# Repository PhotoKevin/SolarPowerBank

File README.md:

# SolarPowerBank
Solar charged power bank

This is a replacement for one I had cobbled together using some ready made boards. The redesign is intended to
address two major areas:

* Airline compatible. Commercial units tend to be all-in-one. You can't separate the battery pack from the solar
panel. This is a problem since you can't put LIon batteries in checked luggage. This unit is designed to be
separate from the panel.
* Fast charge. The old one could only do 500mA charging.  The idea is to keep a battery charging all day and
be able to quick charge a phone.
* Designed to go in a box. If you build something from pre-made boards such as those from AdaFruit, the connectors
are all on the board. This is set up to use "panel mount" connectors.

## Hardware design
The design works around two integrated circuits. A Texas Instruments BQ25185 and an iSmartWare SW2303.

### BQ25185
The TI BQ25185 is a multi-chemistry battery charging controller. The key feature for this application is that it's solar compatible. Solar panels will shut down if you try to draw too much current from them. This can lead to an infinite start/stop cycle which is inefficient and will reduce battery life. [Datasheet](http://www.ti.com/lit/ds/symlink/bq51050b.pdf)

### SW2303
The iSmartWare SW2303 is a fast USB charging module. [Datasheet](http://www.ismartware.cn/upload/goods/20220721/202207211507542921.pdf)

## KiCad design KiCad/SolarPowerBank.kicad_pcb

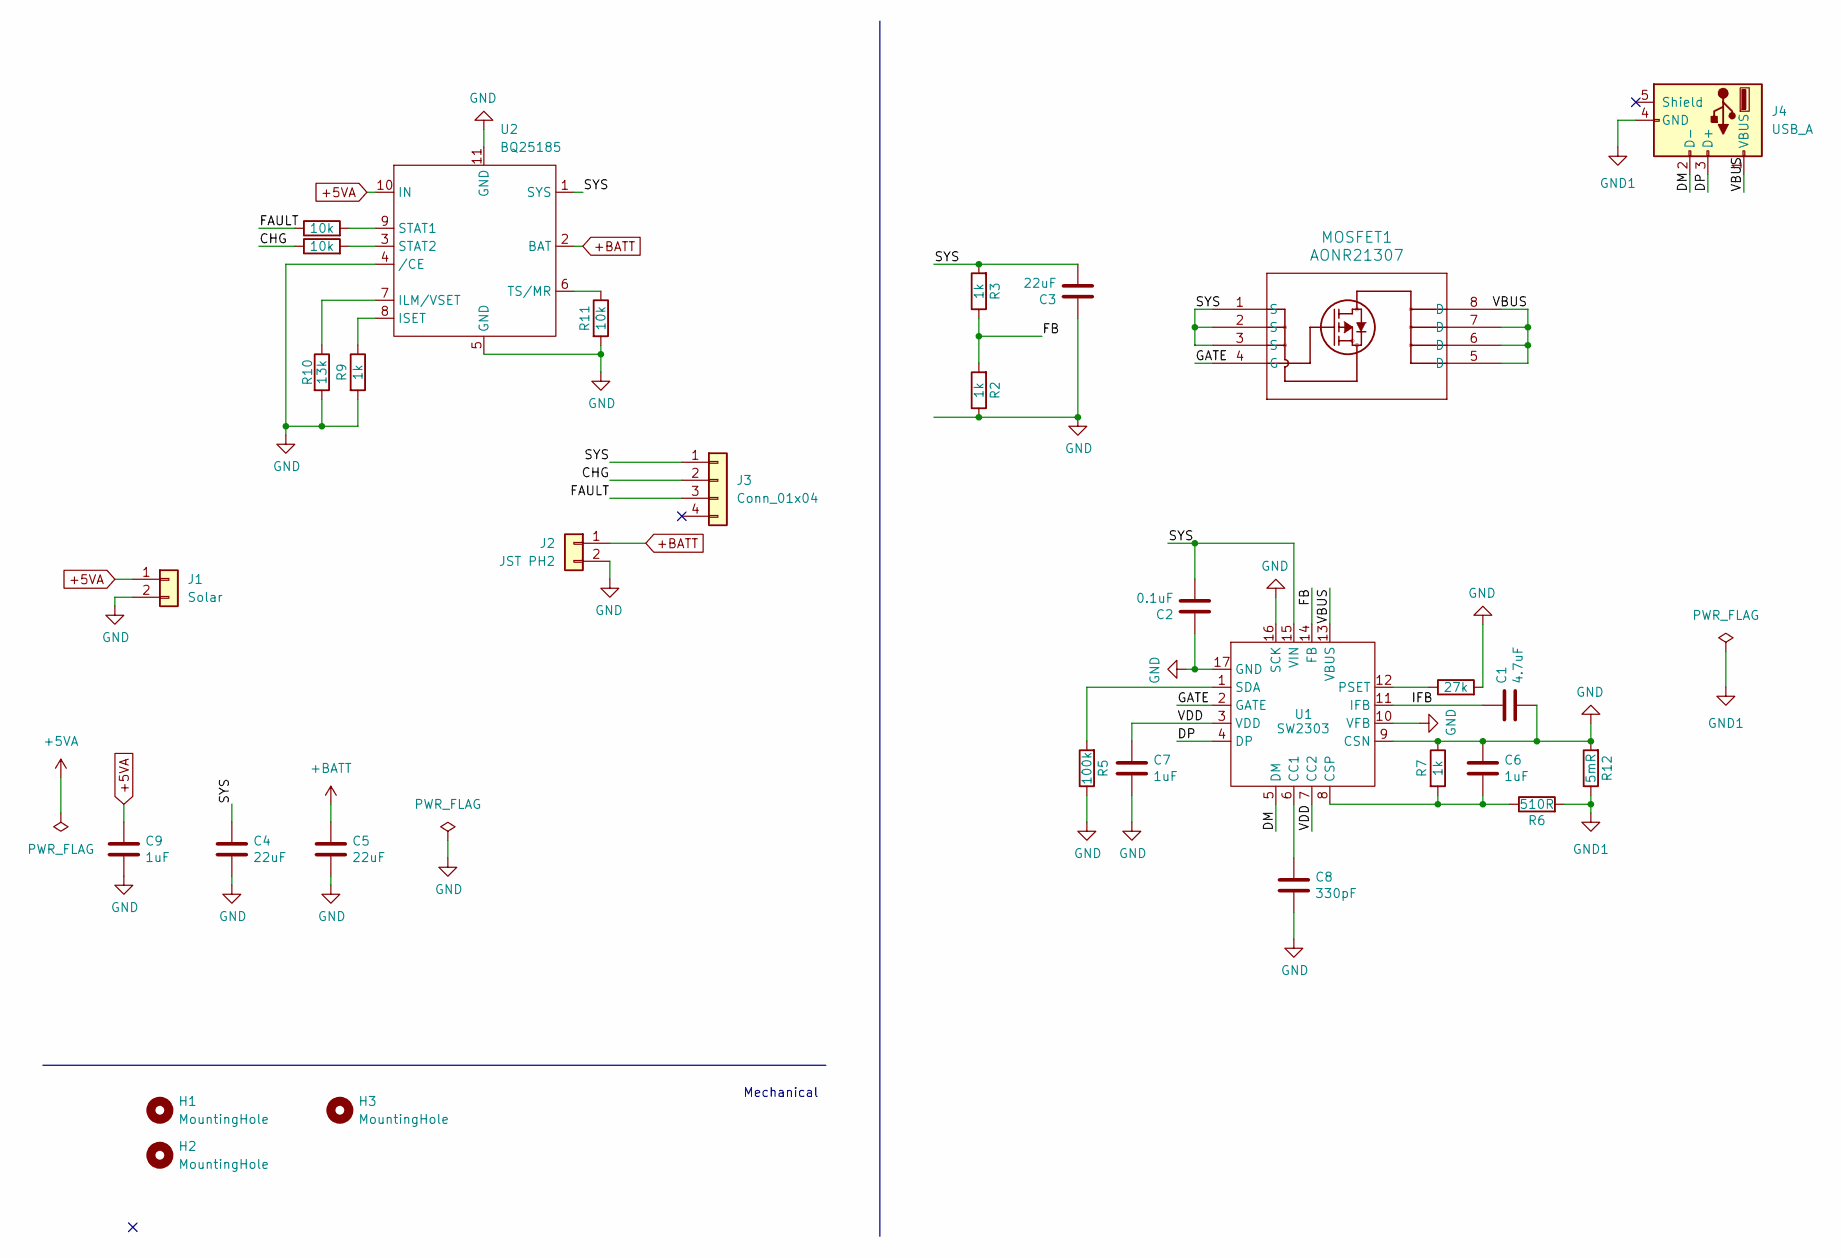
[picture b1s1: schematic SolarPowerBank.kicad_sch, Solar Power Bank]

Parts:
C1: 4.7uF; C_1206_3216Metric_Pad1.33x1.80mm_HandSolder
C2: 0.1uF; C_1206_3216Metric_Pad1.33x1.80mm_HandSolder
C3, C4, C5: 22uF; C_1206_3216Metric_Pad1.33x1.80mm_HandSolder
C6, C7, C9: 1uF; C_1206_3216Metric_Pad1.33x1.80mm_HandSolder
C8: 330pF; C_1206_3216Metric_Pad1.33x1.80mm_HandSolder
H1, H2, H3: MountingHole; MountingHole_3.5mm
J1: Solar; PinHeader_1x02_P2.54mm_Vertical
J2: JST PH2; JST_PH_S2B-PH-K_1x02_P2.00mm_Horizontal
J3: Conn_01x04; PinHeader_2x02_P2.54mm_Vertical
J4: USB_A; PinHeader_1x05_P2.54mm_Vertical
MOSFET1: AONR21307; DFN3x3A_8L_EP1_P
R1: 27k; R_1206_3216Metric_Pad1.30x1.75mm_HandSolder
R2, R3, R7, R9: 1k; R_1206_3216Metric_Pad1.30x1.75mm_HandSolder
R4, R8, R11: 10k; R_1206_3216Metric_Pad1.30x1.75mm_HandSolder
R5: 100k; R_1206_3216Metric_Pad1.30x1.75mm_HandSolder
R6: 510R; R_1206_3216Metric_Pad1.30x1.75mm_HandSolder
R10: 13k; R_1206_3216Metric_Pad1.30x1.75mm_HandSolder
R12: 5mR; R_1206_3216Metric_Pad1.30x1.75mm_HandSolder
U1: SW2303; QFN-16-1EP_4x4mm_P0.65mm_EP2.15x2.15mm_ThermalVias-HandSold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
U2: BQ25185; WSON-10-1EP_2.2x2.0mm_P0.4_ThermalVias-HandSolder

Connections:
+5VA: C9.1, J1.1, U2.10 (IN)
+BATT: C5.1, J2.1, U2.2 (BAT)
/CHG: J3.2, R4.1
/DM: J4.2 (D-), U1.5 (DM)
/DP: J4.3 (D+), U1.4 (DP)
/FAULT: J3.3, R8.1
/FB: R2.2, R3.1, U1.14 (FB)
/GATE: MOSFET1.4 (G), U1.2 (GATE)
/IFB: C1.1, U1.11 (IFB)
/SYS: C2.2, C3.2, C4.1, J3.1, MOSFET1.1 (S), MOSFET1.2 (S), MOSFET1.3 (S), R3.2, U1.15 (VIN), U2.1 (SYS)
/VBUS: J4.1 (VBUS), MOSFET1.5 (D), MOSFET1.6 (D), MOSFET1.7 (D), MOSFET1.8 (D), U1.13 (VBUS)
/VDD: C7.1, U1.3 (VDD), U1.7 (CC2)
GND: C1.2, C2.1, C3.1, C4.2, C5.2, C6.1, C7.2, C8.2, C9.2, J1.2, J2.2, R1.2, R2.1, R5.1, R7.1, R9.2, R10.2, R11.2, R12.2, U1.9 (CSN), U1.10 (VFB), U1.16 (SCK), U1.17 (GND), U2.4 (/CE), U2.5 (GND), U2.11 (GND)
GND1: J4.4 (GND), R6.2, R12.1
unnamed: C8.1, U1.6 (CC1)
unnamed: C6.2, R6.1, R7.2, U1.8 (CSP)
unnamed: R1.1, U1.12 (PSET)
unnamed: R5.2, U1.1 (SDA)
unnamed: R10.1, U2.7 (ILM/VSET)
unnamed: R9.1, U2.8 (ISET)
unnamed: R8.2, U2.9 (STAT1)
unnamed: R4.2, U2.3 (STAT2)
unnamed: R11.1, U2.6 (TS/MR)

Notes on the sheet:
Mechanical

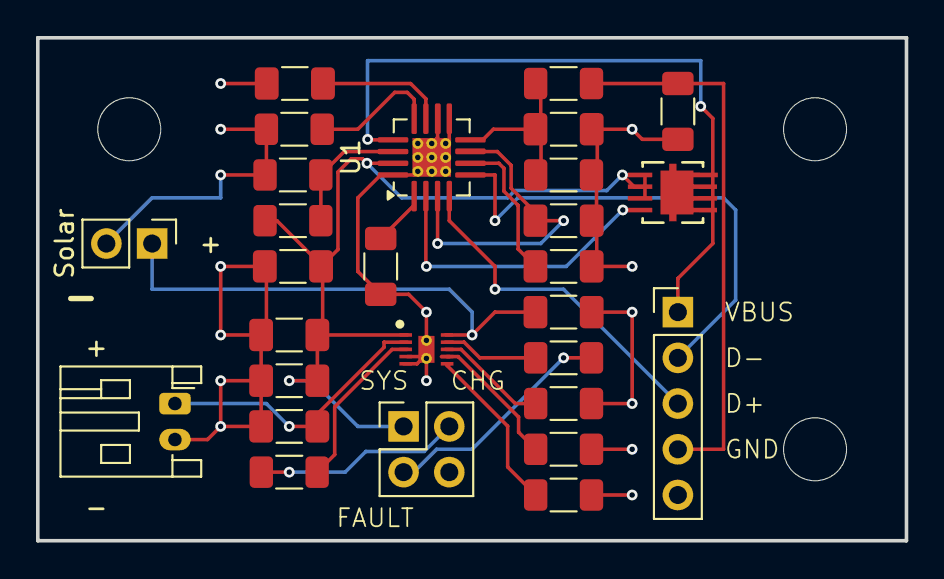
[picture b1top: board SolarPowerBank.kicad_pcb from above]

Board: 2 copper layers, 48.3 x 27.9 mm, 31 parts (0 on the bottom side), 23 nets.

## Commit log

2025-01-03 Initial PCB version. Untested at time of commit.
2025-01-26 Move KiCad files to their own directory.
2025-02-13 Changed footprints to allow for easier hand soldering
